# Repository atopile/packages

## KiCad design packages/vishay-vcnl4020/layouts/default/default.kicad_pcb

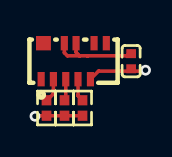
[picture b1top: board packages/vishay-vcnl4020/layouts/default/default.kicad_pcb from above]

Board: 2 copper layers, 5 parts (0 on the bottom side), 5 nets.

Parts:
C1: 1F; C0402
R1, R2, R3: 10000Ω; R0402
U1: SENSOR-SMD_VCNL4020-GS08

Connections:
INT: R3.2, U1.3
SCL: R1.2, U1.4
SDA: R2.2, U1.2
hv: C1.1, R1.1, R2.1, R3.1, U1.5
lv: C1.2, U1.8, U1.9

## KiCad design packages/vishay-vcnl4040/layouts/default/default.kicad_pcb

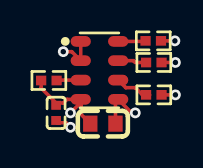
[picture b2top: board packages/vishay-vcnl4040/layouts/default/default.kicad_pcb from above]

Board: 2 copper layers, 7 parts (0 on the bottom side), 6 nets.

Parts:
C1: 2.2e-F; C0603
C2: 1e-06F; C0402
R1, R2, R3: 10000Ω; R0402
R4: 22Ω; R0402
U1: SENSORS-SMD_VCNL4040M3OE

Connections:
INT: R3.1, U1.6
SCL: R1.1, U1.8
SDA: R2.1, U1.7
VDD: R4.1, U1.3
hv: C1.1, C2.1, R1.2, R2.2, R3.2, R4.2, U1.4
lv: C1.2, C2.2, U1.1, U1.2, U1.5

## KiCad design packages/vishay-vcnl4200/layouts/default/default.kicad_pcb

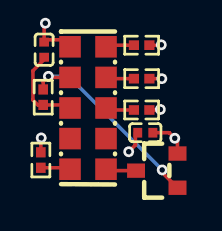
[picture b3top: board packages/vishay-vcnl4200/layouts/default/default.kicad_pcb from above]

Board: 2 copper layers, 9 parts (0 on the bottom side), 8 nets.

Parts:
C1: {1.759..2.64}F; C0402
C2: 1±10.0%F; C0402
Q1: SOT-23_L2.9-W1.3-P1.90-LS2.4-BR
R1, R2, R3, R5: 10000±1.0%Ω; R0402
R4: 2000±1.0%Ω; R0402
U1: SENSOR-SMD_VCNL4200

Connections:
D: Q1.3, U1.6
G: Q1.1, R5.2, U1.2
INT: R3.2, U1.8
LEDneg: R4.1, U1.5
SCL: R1.2, U1.10
SDA: R2.2, U1.9
hv: C1.1, C2.1, Q1.2, R1.1, R2.1, R3.1, R5.1, U1.3
lv: C1.2, C2.2, R4.2, U1.1

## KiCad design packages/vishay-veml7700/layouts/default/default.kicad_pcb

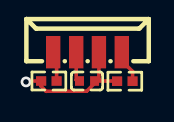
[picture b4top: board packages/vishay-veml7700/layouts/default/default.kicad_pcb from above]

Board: 2 copper layers, 4 parts (0 on the bottom side), 4 nets.

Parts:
C1: 1F; C0402
LED1: LED-SMD_4P-L6.8-W2.4_VEML7700-TR
R1, R2: 10000Ω; R0402

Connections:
SCL: LED1.1, R1.2
SDA: LED1.4, R2.2
hv: C1.1, LED1.2, R1.1, R2.1
lv: C1.2, LED1.3
